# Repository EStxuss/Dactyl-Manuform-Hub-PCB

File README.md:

Wired version has been tested. Wireless version has been ordered from fab and hasn't been tested

I'm not an electrical engineer. I'm open to suggestions for changes
# dactyl-mcu-pcb-mounts
PCBs that can fit with dactyl manuform cases generated with the PCB_MOUNT value for controller_mount_type thats available in kissetfall dactyl case generator fork: https://github.com/kissetfall/dactyl-keyboard

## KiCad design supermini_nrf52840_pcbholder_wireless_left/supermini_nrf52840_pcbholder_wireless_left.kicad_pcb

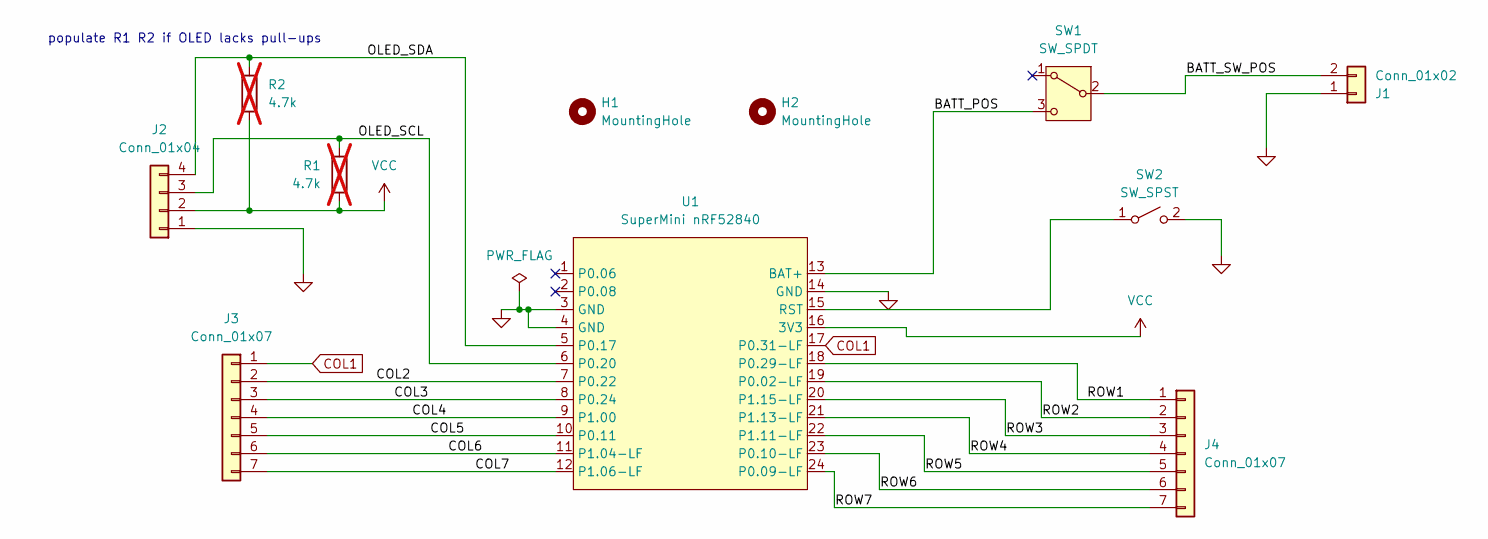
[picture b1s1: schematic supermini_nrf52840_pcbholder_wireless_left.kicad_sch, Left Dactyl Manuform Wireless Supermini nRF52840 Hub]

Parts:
H1, H2: MountingHole; M1.4_tapping_Hole_JLC
J1: Conn_01x02; JST_PH_S2B-PH-K_1x02_P2.00mm_Horizontal
J2: Conn_01x04; JST_PH_S4B-PH-K_1x04_P2.00mm_Horizontal
J3, J4: Conn_01x07; PinHeader_1x07_P2.54mm_Vertical
R1, R2: 4.7k; R_0805_2012Metric; not fitted
SW1: SW_SPDT; SW_SLW-864574-5A-RA-N-D
SW2: SW_SPST; SW_SKHLLCA010
U1: SuperMini nRF52840; SuperMini_nRF52840_H_USBup

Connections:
/BATT_POS: SW1.3 (C), U1.13 (BAT+)
/BATT_SW_POS: J1.2, SW1.2 (B)
/COL2: J3.2, U1.7 (P0.22)
/COL3: J3.3, U1.8 (P0.24)
/COL4: J3.4, U1.9 (P1.00)
/COL5: J3.5, U1.10 (P0.11)
/COL6: J3.6, U1.11 (P1.04-LF)
/COL7: J3.7, U1.12 (P1.06-LF)
/OLED_SCL: J2.3, R1.2, U1.6 (P0.20)
/OLED_SDA: J2.4, R2.2, U1.5 (P0.17)
/ROW1: J4.1, U1.18 (P0.29-LF)
/ROW2: J4.2, U1.19 (P0.02-LF)
/ROW3: J4.3, U1.20 (P1.15-LF)
/ROW4: J4.4, U1.21 (P1.13-LF)
/ROW5: J4.5, U1.22 (P1.11-LF)
/ROW6: J4.6, U1.23 (P0.10-LF)
/ROW7: J4.7, U1.24 (P0.09-LF)
COL1: J3.1, U1.17 (P0.31-LF)
GND: J1.1, J2.1, SW2.2 (B), U1.3 (GND), U1.4 (GND), U1.14 (GND)
unnamed: SW2.1 (A), U1.15 (RST)
VCC: J2.2, R1.1, R2.1, U1.16 (3V3)

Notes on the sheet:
populate R1 R2 if OLED lacks pull-ups

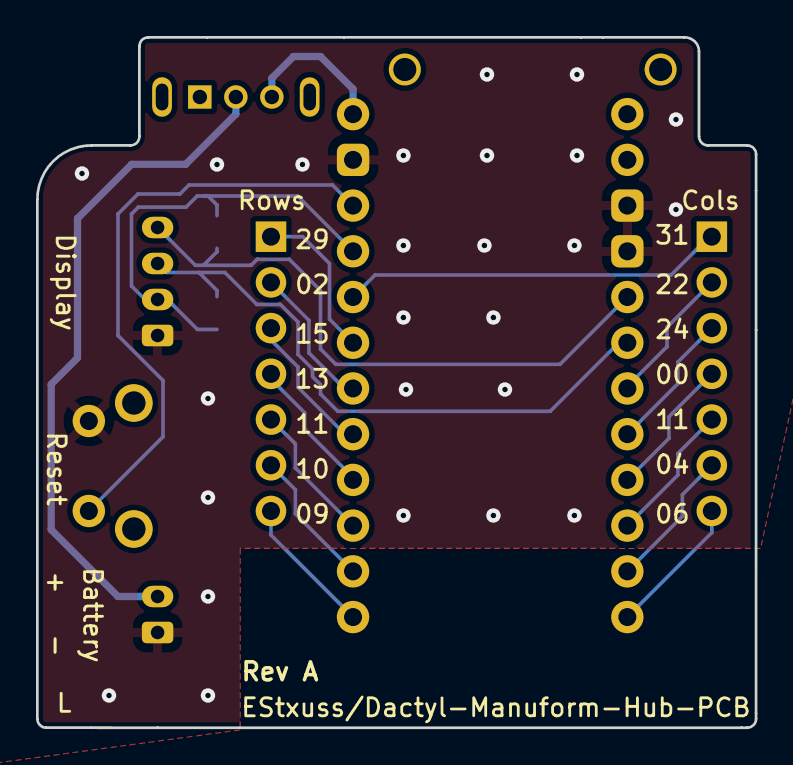
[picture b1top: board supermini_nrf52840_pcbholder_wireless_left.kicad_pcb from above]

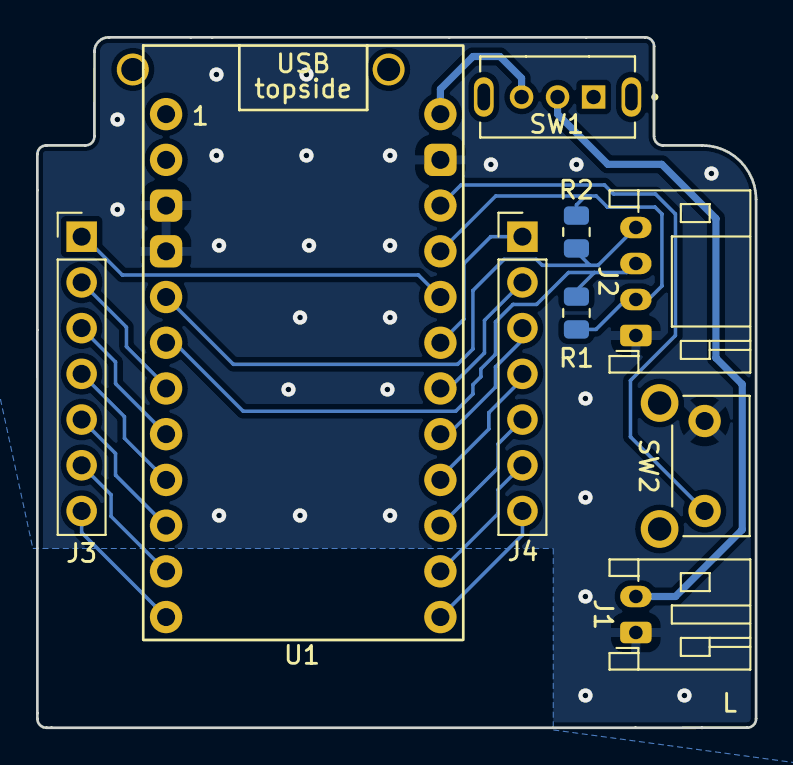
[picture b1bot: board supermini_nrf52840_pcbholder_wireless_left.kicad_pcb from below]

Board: 2 copper layers, 39.9 x 38.4 mm, 11 parts (9 on the bottom side), 21 nets.

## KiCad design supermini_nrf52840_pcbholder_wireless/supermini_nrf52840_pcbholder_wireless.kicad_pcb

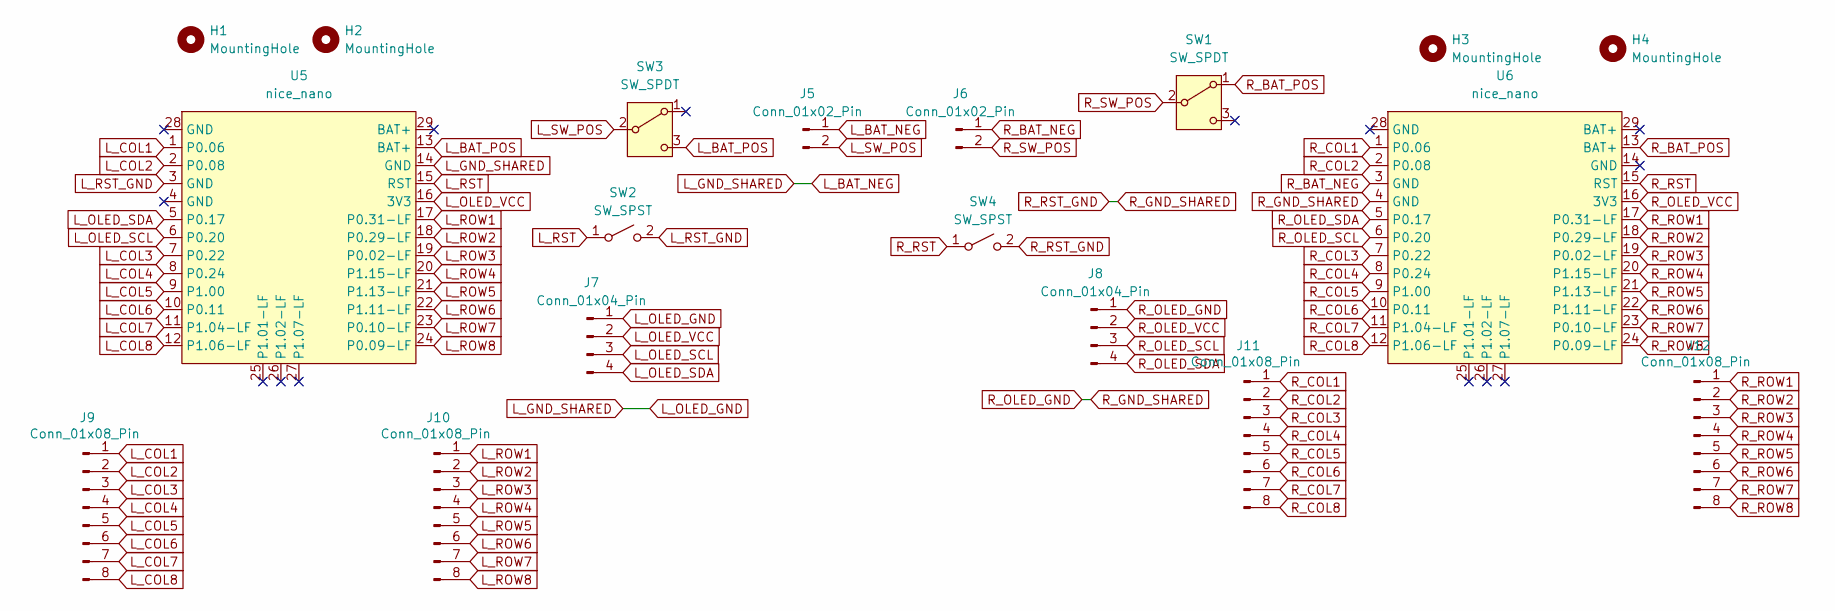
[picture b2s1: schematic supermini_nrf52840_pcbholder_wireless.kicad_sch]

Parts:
H1, H2, H3, H4: MountingHole; M1.4_tapping_Hole_rev2
J5, J6: Conn_01x02_Pin; JST_PH_S2B-PH-K_1x02_P2.00mm_Horizontal
J7, J8: Conn_01x04_Pin; JST_PH_S4B-PH-K_1x04_P2.00mm_Horizontal
J9, J10, J11, J12: Conn_01x08_Pin; PinHeader_1x08_P2.54mm_Vertical_rev2
SW1, SW3: SW_SPDT; SW_SLW-864574-5A-RA-N-D
SW2, SW4: SW_SPST; SW_SKHLLCA010
U5, U6: nice_nano; SuperMini_nRF52840_H_USBup

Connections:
L_BAT_NEG: J5.1, J7.1, U5.14 (GND)
L_BAT_POS: SW3.3 (C), U5.13 (BAT+)
L_COL1: J9.1, U5.1 (P0.06)
L_COL2: J9.2, U5.2 (P0.08)
L_COL3: J9.3, U5.7 (P0.22)
L_COL4: J9.4, U5.8 (P0.24)
L_COL5: J9.5, U5.9 (P1.00)
L_COL6: J9.6, U5.10 (P0.11)
L_COL7: J9.7, U5.11 (P1.04-LF)
L_COL8: J9.8, U5.12 (P1.06-LF)
L_OLED_SCL: J7.3, U5.6 (P0.20)
L_OLED_SDA: J7.4, U5.5 (P0.17)
L_OLED_VCC: J7.2, U5.16 (3V3)
L_ROW1: J10.1, U5.17 (P0.31-LF)
L_ROW2: J10.2, U5.18 (P0.29-LF)
L_ROW3: J10.3, U5.19 (P0.02-LF)
L_ROW4: J10.4, U5.20 (P1.15-LF)
L_ROW5: J10.5, U5.21 (P1.13-LF)
L_ROW6: J10.6, U5.22 (P1.11-LF)
L_ROW7: J10.7, U5.23 (P0.10-LF)
L_ROW8: J10.8, U5.24 (P0.09-LF)
L_RST: SW2.1 (A), U5.15 (RST)
L_RST_GND: SW2.2 (B), U5.3 (GND)
L_SW_POS: J5.2, SW3.2 (B)
R_BAT_NEG: J6.1, U6.3 (GND)
R_BAT_POS: SW1.1 (A), U6.13 (BAT+)
R_COL1: J11.1, U6.1 (P0.06)
R_COL2: J11.2, U6.2 (P0.08)
R_COL3: J11.3, U6.7 (P0.22)
R_COL4: J11.4, U6.8 (P0.24)
R_COL5: J11.5, U6.9 (P1.00)
R_COL6: J11.6, U6.10 (P0.11)
R_COL7: J11.7, U6.11 (P1.04-LF)
R_COL8: J11.8, U6.12 (P1.06-LF)
R_GND_SHARED: J8.1, SW4.2 (B), U6.4 (GND)
R_OLED_SCL: J8.3, U6.6 (P0.20)
R_OLED_SDA: J8.4, U6.5 (P0.17)
R_OLED_VCC: J8.2, U6.16 (3V3)
R_ROW1: J12.1, U6.17 (P0.31-LF)
R_ROW2: J12.2, U6.18 (P0.29-LF)
R_ROW3: J12.3, U6.19 (P0.02-LF)
R_ROW4: J12.4, U6.20 (P1.15-LF)
R_ROW5: J12.5, U6.21 (P1.13-LF)
R_ROW6: J12.6, U6.22 (P1.11-LF)
R_ROW7: J12.7, U6.23 (P0.10-LF)
R_ROW8: J12.8, U6.24 (P0.09-LF)
R_RST: SW4.1 (A), U6.15 (RST)
R_SW_POS: J6.2, SW1.2 (B)

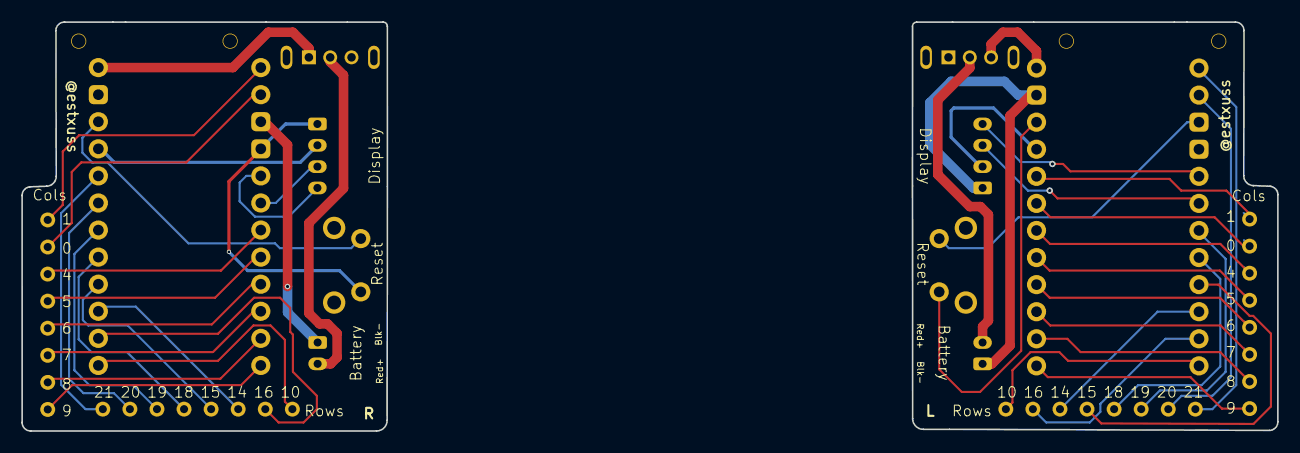
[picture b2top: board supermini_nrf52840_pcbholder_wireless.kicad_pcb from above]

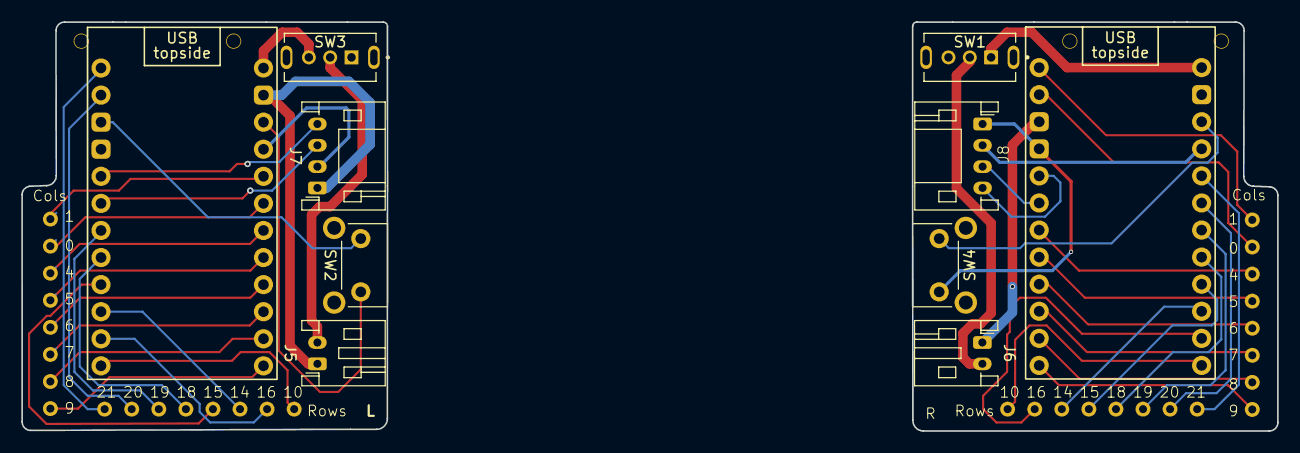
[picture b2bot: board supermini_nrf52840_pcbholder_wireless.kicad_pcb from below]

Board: 2 copper layers, 117.8 x 38.4 mm, 18 parts (14 on the bottom side), 48 nets.

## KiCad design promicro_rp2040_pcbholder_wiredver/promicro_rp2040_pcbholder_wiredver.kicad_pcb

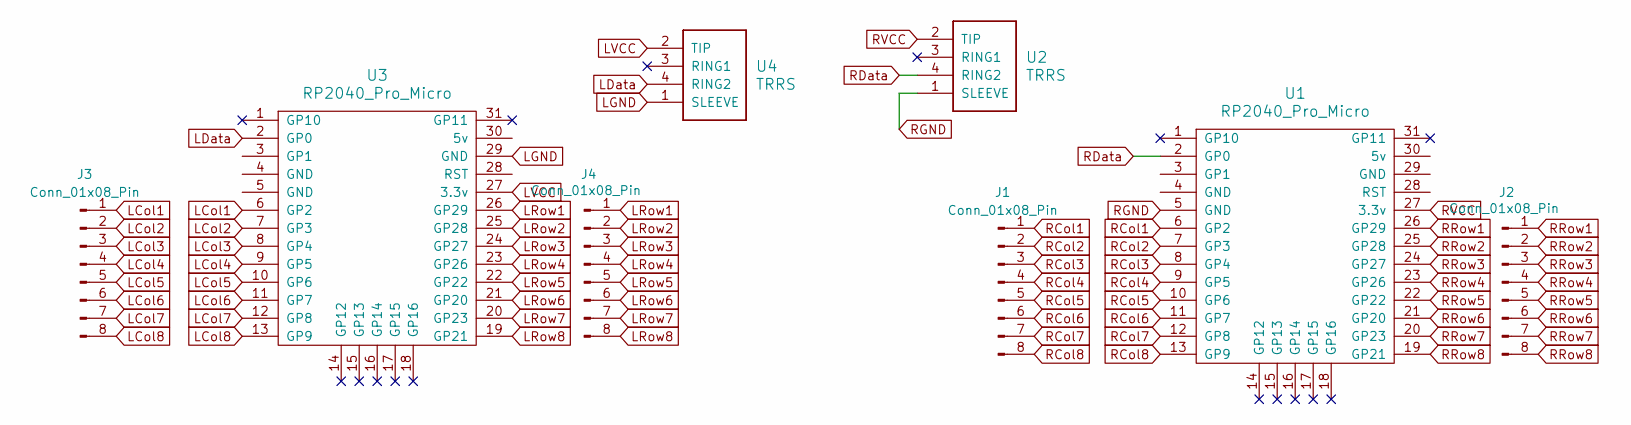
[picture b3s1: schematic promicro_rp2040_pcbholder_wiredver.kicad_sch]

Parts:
J1, J2, J3, J4: Conn_01x08_Pin; PinHeader_1x08_P2.54mm_Vertical_rev2
U1, U3: RP2040_Pro_Micro
U2, U4: TRRS; TRRS_PJ-320A

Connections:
LCol1: J3.1, U3.6 (GP2)
LCol2: J3.2, U3.7 (GP3)
LCol3: J3.3, U3.8 (GP4)
LCol4: J3.4, U3.9 (GP5)
LCol5: J3.5, U3.10 (GP6)
LCol6: J3.6, U3.11 (GP7)
LCol7: J3.7, U3.12 (GP8)
LCol8: J3.8, U3.13 (GP9)
LData: U3.2 (GP0), U4.4 (RING2)
LGND: U3.29 (GND), U4.1 (SLEEVE)
LRow1: J4.1, U3.26 (GP29)
LRow2: J4.2, U3.25 (GP28)
LRow3: J4.3, U3.24 (GP27)
LRow4: J4.4, U3.23 (GP26)
LRow5: J4.5, U3.22 (GP22)
LRow6: J4.6, U3.21 (GP20)
LRow7: J4.7, U3.20 (GP23)
LRow8: J4.8, U3.19 (GP21)
LVCC: U3.27 (3.3v), U4.2 (TIP)
RCol1: J1.1, U1.6 (GP2)
RCol2: J1.2, U1.7 (GP3)
RCol3: J1.3, U1.8 (GP4)
RCol4: J1.4, U1.9 (GP5)
RCol5: J1.5, U1.10 (GP6)
RCol6: J1.6, U1.11 (GP7)
RCol7: J1.7, U1.12 (GP8)
RCol8: J1.8, U1.13 (GP9)
RData: U1.2 (GP0), U2.4 (RING2)
RGND: U1.5 (GND), U2.1 (SLEEVE)
RRow1: J2.1, U1.26 (GP29)
RRow2: J2.2, U1.25 (GP28)
RRow3: J2.3, U1.24 (GP27)
RRow4: J2.4, U1.23 (GP26)
RRow5: J2.5, U1.22 (GP22)
RRow6: J2.6, U1.21 (GP20)
RRow7: J2.7, U1.20 (GP23)
RRow8: J2.8, U1.19 (GP21)
RVCC: U1.27 (3.3v), U2.2 (TIP)

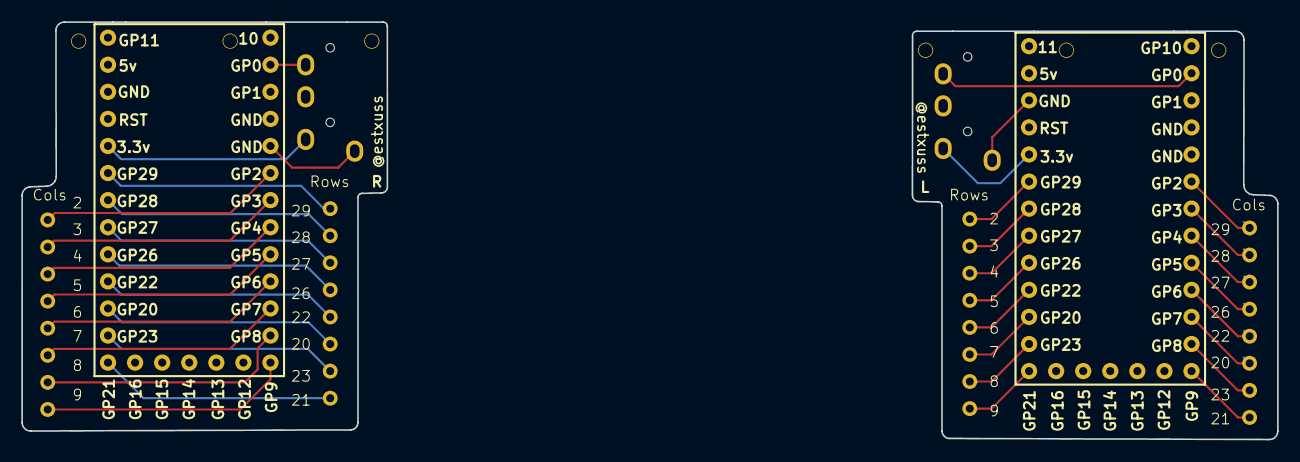
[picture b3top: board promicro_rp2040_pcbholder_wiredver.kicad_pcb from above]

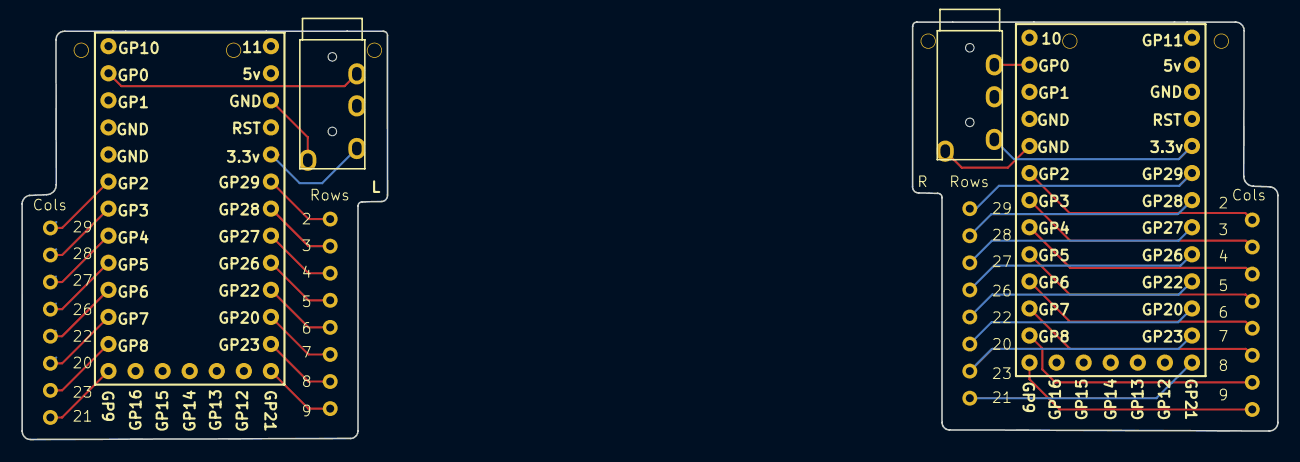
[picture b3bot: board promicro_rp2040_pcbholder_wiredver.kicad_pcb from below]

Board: 2 copper layers, 117.8 x 39.2 mm, 8 parts (8 on the bottom side), 38 nets.

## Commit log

2025-01-01 rp2040 promicro holder partial completion
2025-01-01 schematic naming
2025-01-02 initial design done. Ordered for testing
2025-01-20 tested working. Swap left side pcb's rows and cols wire holes
2025-02-09 slight change m1.4 right side pcb hole spacing
2025-02-25 add supermini nrf52840 pcb holder for zmk wireless dactyls
2025-03-03 change power switch footprint and supermini board placement
2025-03-08 mostly done supermini wireless hub version
2025-03-10 add optional i2c pull ups
2025-03-10 edge cuts change
2025-03-11 create left side and tweaks
2025-03-11 remove unused pins from supermini symbol
